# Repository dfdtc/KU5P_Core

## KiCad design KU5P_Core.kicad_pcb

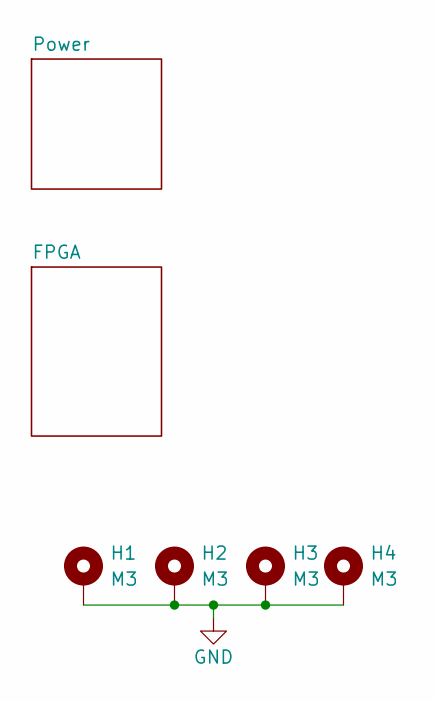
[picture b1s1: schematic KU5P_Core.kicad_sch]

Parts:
H1, H2, H3, H4: M3; MountingHole_3mm_Pad_TopBottom

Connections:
GND: H1.1 (1_1), H2.1 (1_1), H3.1 (1_1), H4.1 (1_1); also elsewhere on the board

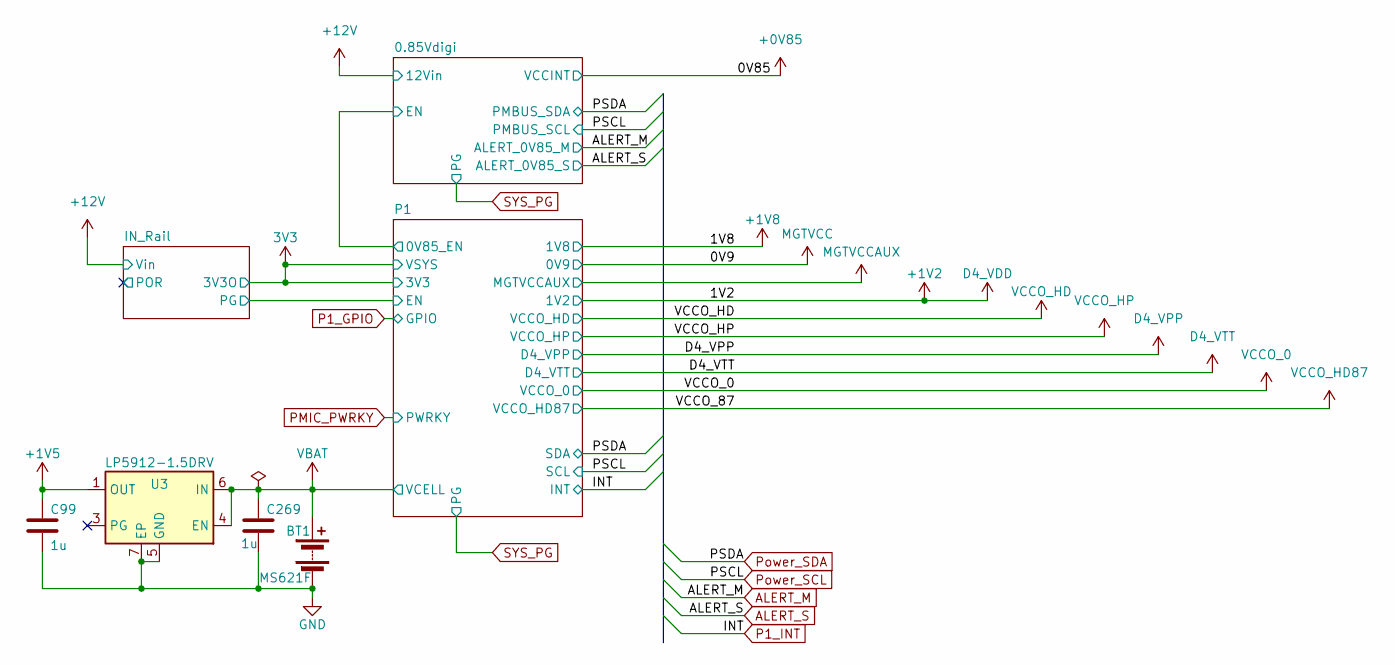
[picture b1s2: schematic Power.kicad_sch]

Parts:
BT1: MS621F; BatteryHolder_Seiko_MS621F
C99, C269: 1u; C_0402_1005Metric
U3: LP5912-1.5DRV; WSON-6-1EP_2x2mm_P0.65mm_EP1x1.6mm

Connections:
+1V5: C99.1, U3.1 (OUT); also elsewhere on the board
GND: BT1.2 (-), C99.2, C269.2, U3.5 (GND), U3.7 (EP); also elsewhere on the board
VBAT: BT1.1 (+), C269.1, U3.4 (EN), U3.6 (IN); also elsewhere on the board

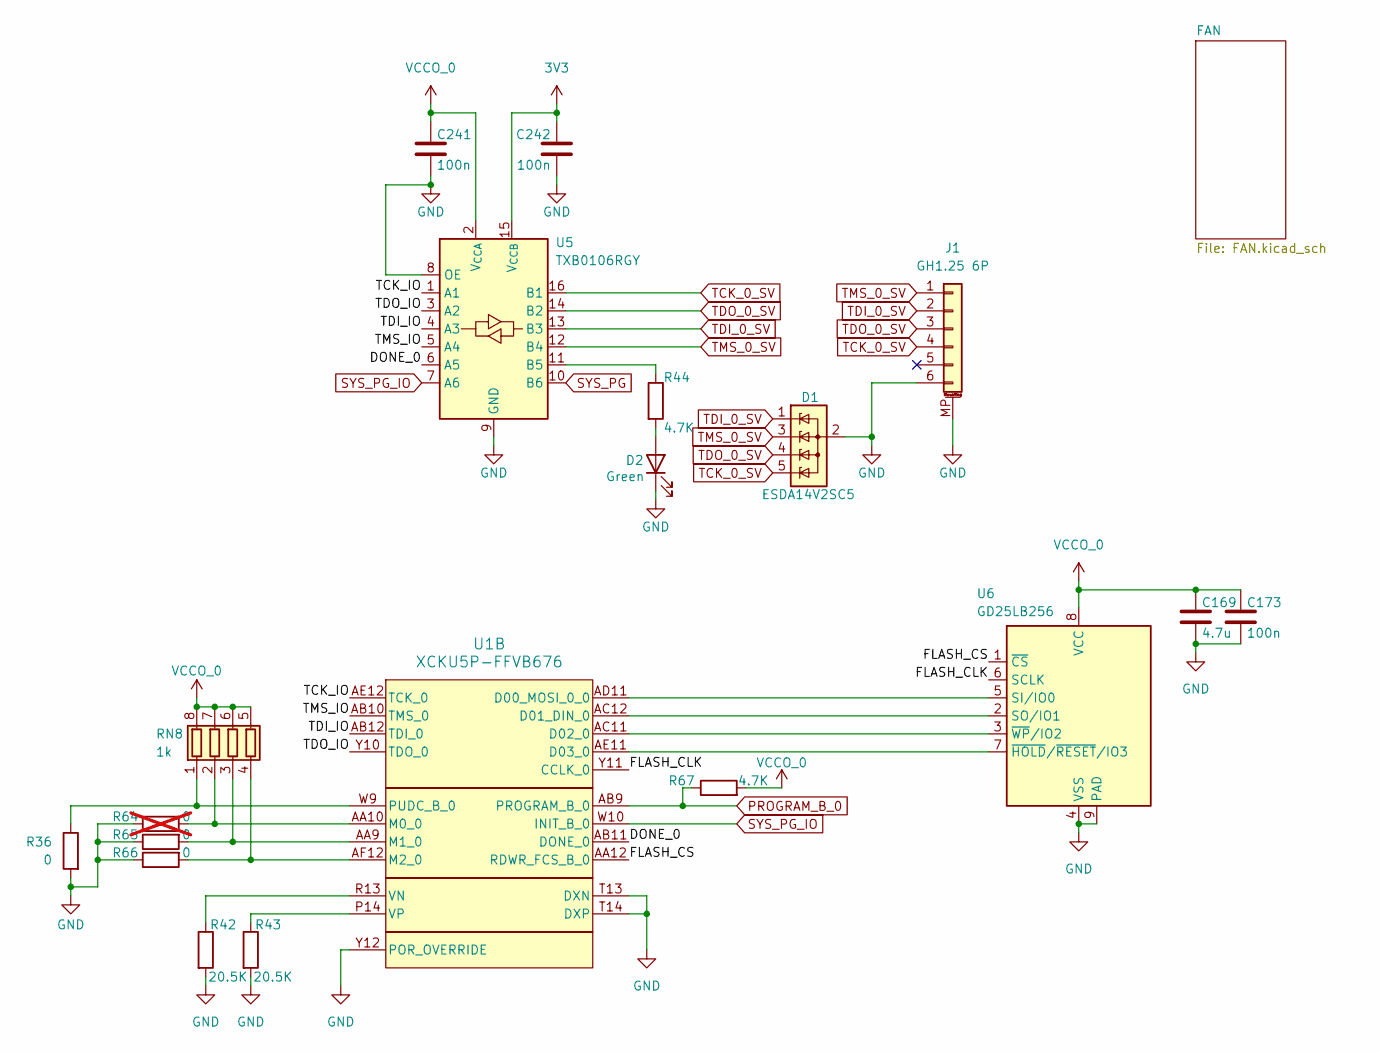
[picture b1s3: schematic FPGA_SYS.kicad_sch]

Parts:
C169: 4.7u; C_0201_0603Metric
C173, C241, C242: 100n; C_0201_0603Metric
D1: ESDA14V2SC5; SOT-23-5
D2: Green; LED_0603_1608Metric
J1: GH1.25 6P; JST_GH_SM06B-GHS-TB_1x06-1MP_P1.25mm_Horizontal
R36, R65, R66: 0; R_0402_1005Metric
R42, R43: 20.5K; R_0201_0603Metric
R44, R67: 4.7K; R_0201_0603Metric
R64: 0; R_0402_1005Metric; not fitted
RN8: 1k; R_Array_Concave_4x0402
U1: XCKU5P-FFVB676; Xilinx_FFG676
U5: TXB0106RGY; Texas_RGY_R-PVQFN-N16_EP2.05x2.55mm
U6: GD25LB256; WSON-8-1EP_8x6mm_P1.27mm_EP3.4x4.3mm

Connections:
3V3: C242.1, U5.15 (V_{CCB}); also elsewhere on the board
/FPGA/FPGA_SYS/DONE_0: U1.AB11 (DONE_0), U5.6 (A5)
/FPGA/FPGA_SYS/FLASH_CLK: U1.Y11 (CCLK_0), U6.6 (SCLK)
/FPGA/FPGA_SYS/FLASH_CS: U1.AA12 (RDWR_FCS_B_0), U6.1 (~CS)
/FPGA/FPGA_SYS/TCK_IO: U1.AE12 (TCK_0), U5.1 (A1)
/FPGA/FPGA_SYS/TDI_IO: U1.AB12 (TDI_0), U5.4 (A3)
/FPGA/FPGA_SYS/TDO_IO: U1.Y10 (TDO_0), U5.3 (A2)
/FPGA/FPGA_SYS/TMS_IO: U1.AB10 (TMS_0), U5.5 (A4)
GND: C169.2, C173.2, C241.2, C242.2, D1.2 (A), D2.1 (K), J1.6, J1.MP (MountPin), R36.2, R42.2, R43.2, R64.1, R65.1, R66.1, U1.T13 (DXN), U1.T14 (DXP), U1.Y12 (POR_OVERRIDE), U5.8 (OE), U5.9 (GND), U5.17 (GND), U6.4 (VSS), U6.9 (PAD); also elsewhere on the board
unnamed: D2.2 (A), R44.2
unnamed: R36.1, RN8.1 (R1.1), U1.W9 (PUDC_B_0)
unnamed: R64.2, RN8.2 (R2.1), U1.AA10 (M0_0)
unnamed: R65.2, RN8.3 (R3.1), U1.AA9 (M1_0)
unnamed: R66.2, RN8.4 (R4.1), U1.AF12 (M2_0)
unnamed: U1.AD11 (D00_MOSI_0_0), U6.5 (SI/IO0)
unnamed: U1.AC12 (D01_DIN_0), U6.2 (SO/IO1)
unnamed: U1.AC11 (D02_0), U6.3 (~WP/IO2)
unnamed: U1.AE11 (D03_0), U6.7 (~HOLD/~RESET/IO3)
unnamed: R42.1, U1.R13 (VN)
unnamed: R43.1, U1.P14 (VP)
unnamed: R44.1, U5.11 (B5)
PROGRAM_B_0: R67.1, U1.AB9 (PROGRAM_B_0); also elsewhere on the board
SYS_PG: U5.10 (B6); also elsewhere on the board
SYS_PG_IO: U1.W10 (INIT_B_0), U5.7 (A6)
TCK_0_SV: D1.5 (K), J1.4, U5.16 (B1)
TDI_0_SV: D1.1 (K), J1.2, U5.13 (B3)
TDO_0_SV: D1.4 (K), J1.3, U5.14 (B2)
TMS_0_SV: D1.3 (K), J1.1, U5.12 (B4)
VCCO_0: C169.1, C173.1, C241.1, R67.2, RN8.5 (R4.2), RN8.6 (R3.2), RN8.7 (R2.2), RN8.8 (R1.2), U5.2 (V_{CCA}), U6.8 (VCC); also elsewhere on the board

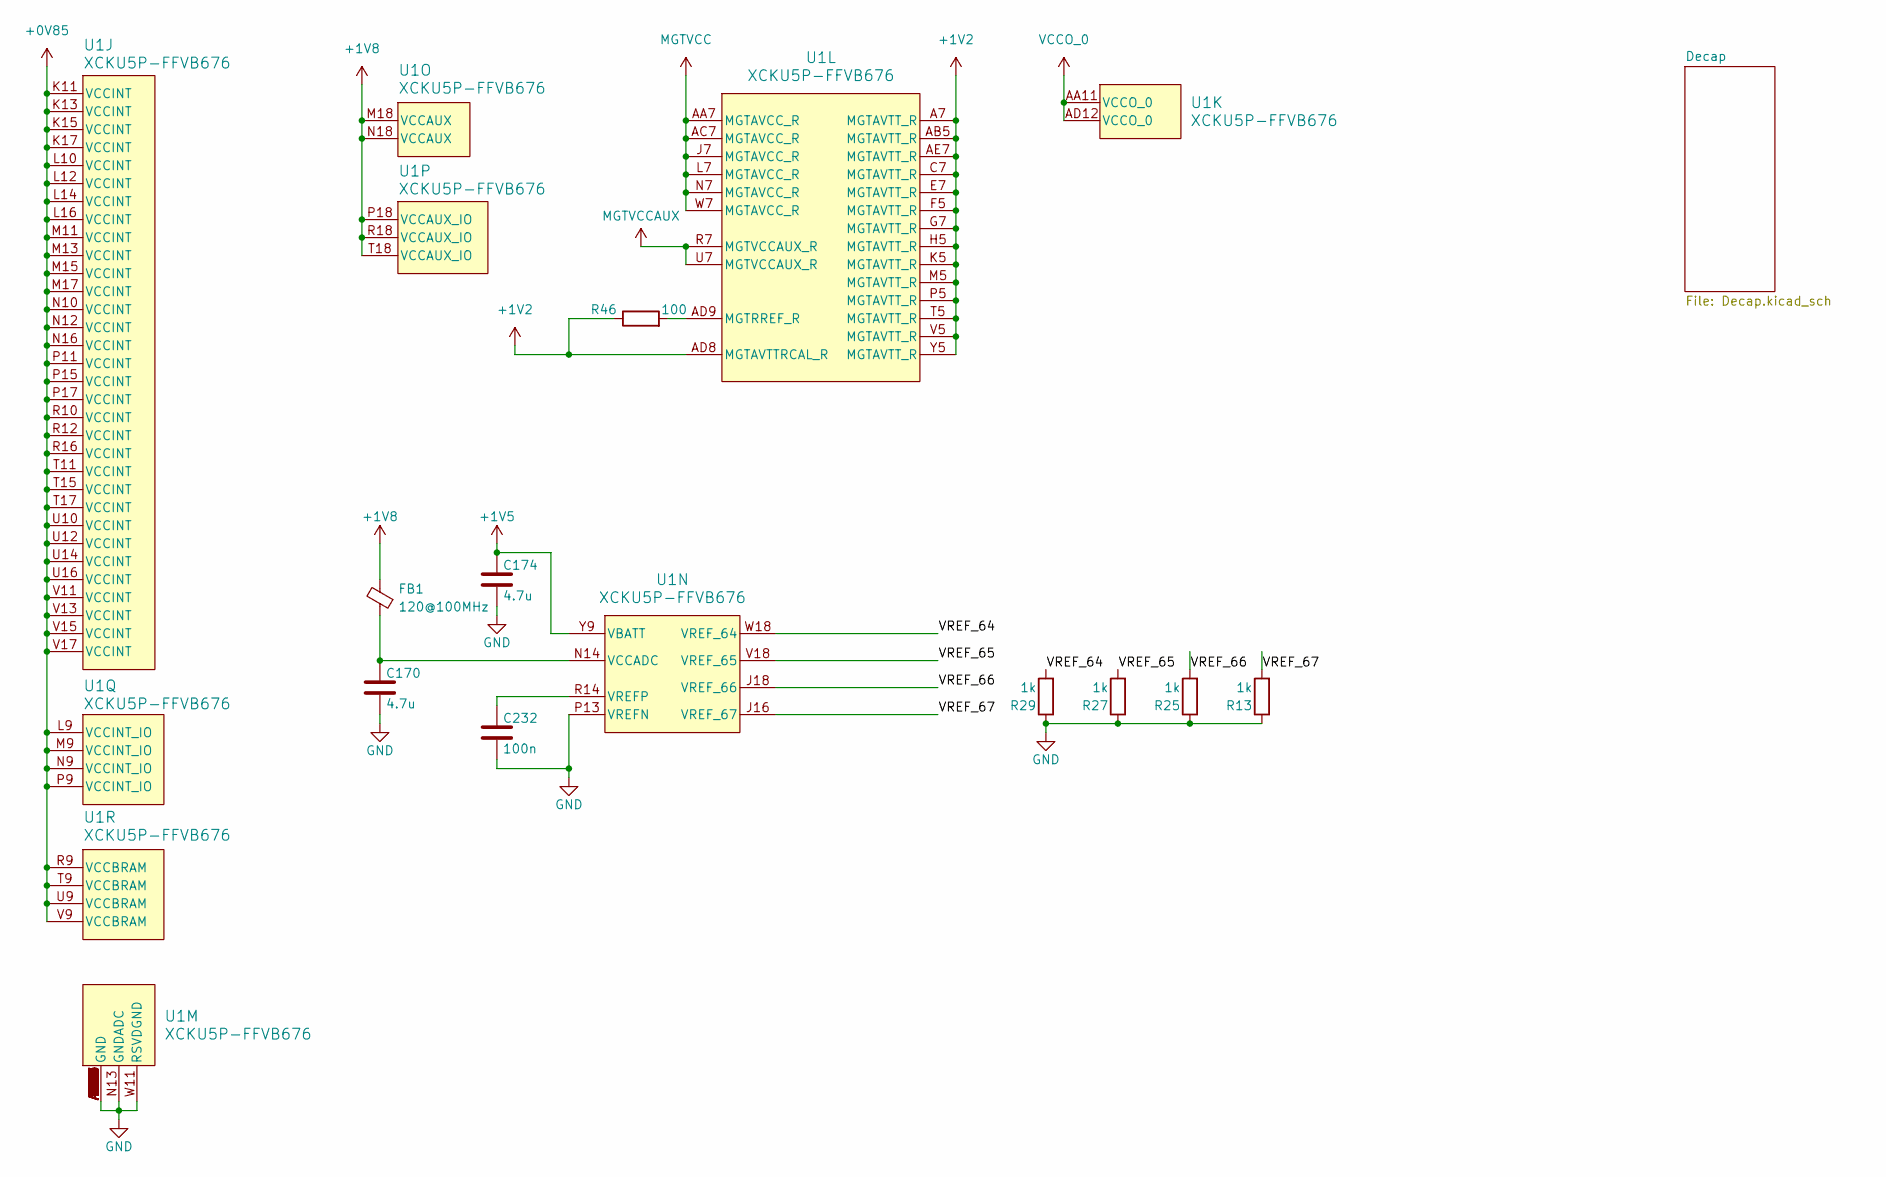
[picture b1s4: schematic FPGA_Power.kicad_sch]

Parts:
C170, C174: 4.7u; C_0201_0603Metric
C232: 100n; C_0201_0603Metric
FB1: 120@100MHz; C_0402_1005Metric
R13, R25, R27, R29: 1k; R_0201_0603Metric
R46: 100; C_0201_0603Metric
U1: XCKU5P-FFVB676; Xilinx_FFG676

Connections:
+0V85: U1.K11 (VCCINT), U1.K13 (VCCINT), U1.K15 (VCCINT), U1.K17 (VCCINT), U1.L9 (VCCINT_IO), U1.L10 (VCCINT), U1.L12 (VCCINT), U1.L14 (VCCINT), U1.L16 (VCCINT), U1.M9 (VCCINT_IO), U1.M11 (VCCINT), U1.M13 (VCCINT), U1.M15 (VCCINT), U1.M17 (VCCINT), U1.N9 (VCCINT_IO), U1.N10 (VCCINT), U1.N12 (VCCINT), U1.N16 (VCCINT), U1.P9 (VCCINT_IO), U1.P11 (VCCINT), U1.P15 (VCCINT), U1.P17 (VCCINT), U1.R9 (VCCBRAM), U1.R10 (VCCINT), U1.R12 (VCCINT), U1.R16 (VCCINT), U1.T9 (VCCBRAM), U1.T11 (VCCINT), U1.T15 (VCCINT), U1.T17 (VCCINT), U1.U9 (VCCBRAM), U1.U10 (VCCINT), U1.U12 (VCCINT), U1.U14 (VCCINT), U1.U16 (VCCINT), U1.V9 (VCCBRAM), U1.V11 (VCCINT), U1.V13 (VCCINT), U1.V15 (VCCINT), U1.V17 (VCCINT); also elsewhere on the board
+1V5: C174.1, U1.Y9 (VBATT); also elsewhere on the board
+1V8: FB1.2, U1.M18 (VCCAUX), U1.N18 (VCCAUX), U1.P18 (VCCAUX_IO), U1.R18 (VCCAUX_IO), U1.T18 (VCCAUX_IO); also elsewhere on the board
/FPGA/FPGA_Power/VREF_64: R29.2, U1.W18 (VREF_64)
/FPGA/FPGA_Power/VREF_65: R27.2, U1.V18 (VREF_65)
/FPGA/FPGA_Power/VREF_66: R25.2, U1.J18 (VREF_66)
/FPGA/FPGA_Power/VREF_67: R13.2, U1.J16 (VREF_67)
GND: C170.2, C174.2, C232.2, R13.1, R25.1, R27.1, R29.1, U1.A1 (GND), U1.A2 (GND), U1.A5 (GND), U1.A6 (GND), U1.A8 (GND), U1.A11 (GND), U1.A16 (GND), U1.A21 (GND), U1.A26 (GND), U1.AA1 (GND), U1.AA2 (GND), U1.AA3 (GND), U1.AA6 (GND), U1.AA8 (GND), U1.AA16 (GND), U1.AA26 (GND), U1.AB3 (GND), U1.AB4 (GND), U1.AB8 (GND), U1.AB13 (GND), U1.AB23 (GND), U1.AC1 (GND), U1.AC2 (GND), U1.AC3 (GND), U1.AC6 (GND), U1.AC8 (GND), U1.AC9 (GND), U1.AC10 (GND), U1.AC20 (GND), U1.AC25 (GND), U1.AD3 (GND), U1.AD4 (GND), U1.AD5 (GND), U1.AD10 (GND), U1.AD17 (GND), U1.AE1 (GND), U1.AE2 (GND), U1.AE5 (GND), U1.AE6 (GND), U1.AE10 (GND), U1.AE14 (GND), U1.AE19 (GND), U1.AE24 (GND), U1.AF3 (GND), U1.AF4 (GND), U1.AF5 (GND), U1.AF8 (GND), U1.AF9 (GND), U1.AF10 (GND), U1.AF11 (GND), U1.AF16 (GND), U1.AF21 (GND), U1.AF26 (GND), U1.B3 (GND), U1.B4 (GND), U1.B5 (GND), U1.B8 (GND), U1.B13 (GND), U1.B18 (GND), U1.B23 (GND), U1.C1 (GND), U1.C2 (GND), U1.C5 (GND), U1.C6 (GND), U1.C8 (GND), U1.C10 (GND), U1.C15 (GND), U1.C25 (GND), U1.D3 (GND), U1.D4 (GND), U1.D5 (GND), U1.D8 (GND), U1.D12 (GND), U1.D22 (GND), U1.E1 (GND), U1.E2 (GND), U1.E3 (GND), U1.E6 (GND), U1.E8 (GND), U1.E19 (GND), U1.F3 (GND), U1.F4 (GND), U1.F8 (GND), U1.F11 (GND), U1.F16 (GND), U1.F21 (GND), U1.F26 (GND), U1.G1 (GND), U1.G2 (GND), U1.G3 (GND), U1.G6 (GND), U1.G8 (GND), U1.G13 (GND), U1.G23 (GND), U1.H3 (GND), U1.H4 (GND), U1.H8 (GND), U1.H20 (GND), U1.J1 (GND), U1.J2 (GND), U1.J3 (GND), U1.J6 (GND), U1.J8 (GND), U1.J17 (GND), U1.K3 (GND), U1.K4 (GND), U1.K8 (GND), U1.K12 (GND), U1.K14 (GND), U1.K16 (GND), U1.K19 (GND), U1.K24 (GND), U1.L1 (GND), U1.L2 (GND), U1.L3 (GND), U1.L6 (GND), U1.L8 (GND), U1.L11 (GND), U1.L13 (GND), U1.L15 (GND), U1.L17 (GND), U1.L21 (GND), U1.L26 (GND), U1.M3 (GND), U1.M4 (GND), U1.M8 (GND), U1.M10 (GND), U1.M12 (GND), U1.M14 (GND), U1.M16 (GND), U1.M23 (GND), U1.N1 (GND), U1.N2 (GND), U1.N3 (GND), U1.N6 (GND), U1.N8 (GND), U1.N11 (GND), U1.N13 (GNDADC), U1.N15 (GND), U1.N17 (GND), U1.N20 (GND), U1.N25 (GND), U1.P3 (GND), U1.P4 (GND), U1.P8 (GND), U1.P10 (GND), U1.P12 (GND), U1.P13 (VREFN), U1.P16 (GND), U1.R1 (GND), U1.R2 (GND), U1.R3 (GND), U1.R6 (GND), U1.R8 (GND), U1.R11 (GND), U1.R15 (GND), U1.R17 (GND), U1.R19 (GND), U1.R24 (GND), U1.T3 (GND), U1.T4 (GND), U1.T8 (GND), U1.T10 (GND), U1.T12 (GND), U1.T16 (GND), U1.T21 (GND), U1.T26 (GND), U1.U1 (GND), U1.U2 (GND), U1.U3 (GND), U1.U6 (GND), U1.U8 (GND), U1.U11 (GND), U1.U13 (GND), U1.U15 (GND), U1.U17 (GND), U1.U18 (GND), U1.V3 (GND), U1.V4 (GND), U1.V8 (GND), U1.V10 (GND), U1.V12 (GND), U1.V14 (GND), U1.V16 (GND), U1.V20 (GND), U1.V25 (GND), U1.W1 (GND), U1.W2 (GND), U1.W3 (GND), U1.W6 (GND), U1.W8 (GND), U1.W11 (RSVDGND), U1.W17 (GND), U1.W22 (GND), U1.Y3 (GND), U1.Y4 (GND), U1.Y8 (GND), U1.Y19 (GND); also elsewhere on the board
MGTVCC: U1.AA7 (MGTAVCC_R), U1.AC7 (MGTAVCC_R), U1.J7 (MGTAVCC_R), U1.L7 (MGTAVCC_R), U1.N7 (MGTAVCC_R), U1.W7 (MGTAVCC_R); also elsewhere on the board
MGTVCCAUX: U1.R7 (MGTVCCAUX_R), U1.U7 (MGTVCCAUX_R); also elsewhere on the board
unnamed: R46.2, U1.AD9 (MGTRREF_R)
unnamed: C170.1, FB1.1, U1.N14 (VCCADC)
unnamed: C232.1, U1.R14 (VREFP)
VCCO_0: U1.AA11 (VCCO_0), U1.AD12 (VCCO_0); also elsewhere on the board

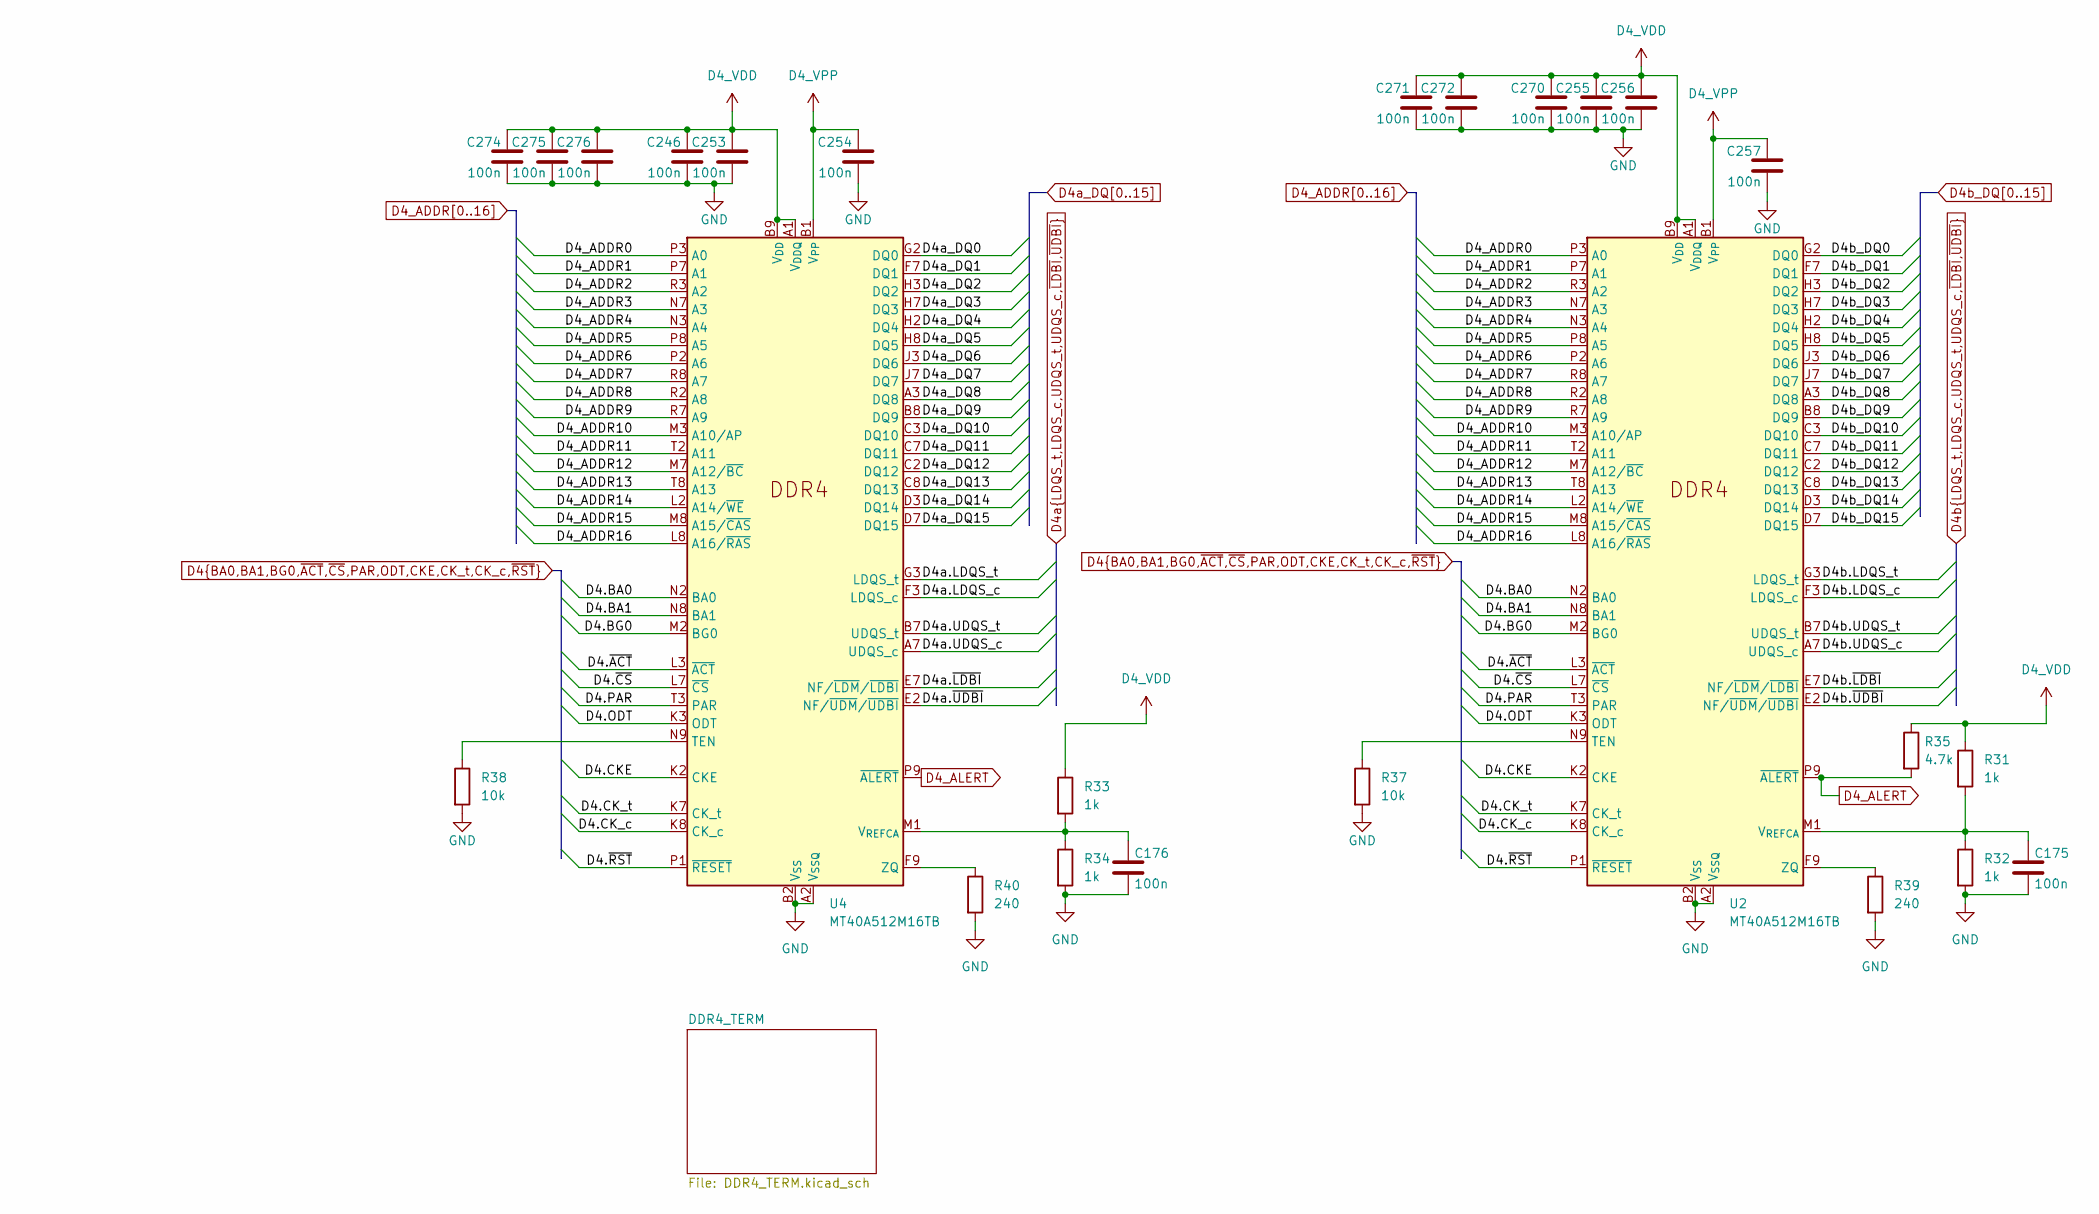
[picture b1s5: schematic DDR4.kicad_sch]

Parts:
C175, C176, C246, C253, C254, C255, C256, C257, C270, C271, C272, C274, C275, C276: 100n; C_0201_0603Metric
R31, R32, R33, R34: 1k; R_0201_0603Metric
R35: 4.7k; R_0201_0603Metric
R37, R38: 10k; R_0201_0603Metric
R39, R40: 240; R_0201_0603Metric
U2, U4: MT40A512M16TB; FBGA-96_7.5x13mm_Layout9x16_P0.8mm

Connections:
D4.BA0: U2.N2 (BA0), U4.N2 (BA0); also elsewhere on the board
D4.BA1: U2.N8 (BA1), U4.N8 (BA1); also elsewhere on the board
D4.BG0: U2.M2 (BG0), U4.M2 (BG0); also elsewhere on the board
D4.CKE: U2.K2 (CKE), U4.K2 (CKE); also elsewhere on the board
D4.CK_c: U2.K8 (CK_c), U4.K8 (CK_c); also elsewhere on the board
D4.CK_t: U2.K7 (CK_t), U4.K7 (CK_t); also elsewhere on the board
D4.ODT: U2.K3 (ODT), U4.K3 (ODT); also elsewhere on the board
D4.PAR: U2.T3 (PAR), U4.T3 (PAR); also elsewhere on the board
D4.~ACT: U2.L3 (~ACT), U4.L3 (~ACT); also elsewhere on the board
D4.~CS: U2.L7 (~CS), U4.L7 (~CS); also elsewhere on the board
D4.~RST: U2.P1 (~RESET), U4.P1 (~RESET); also elsewhere on the board
D4_ADDR0: U2.P3 (A0), U4.P3 (A0); also elsewhere on the board
D4_ADDR1: U2.P7 (A1), U4.P7 (A1); also elsewhere on the board
D4_ADDR2: U2.R3 (A2), U4.R3 (A2); also elsewhere on the board
D4_ADDR3: U2.N7 (A3), U4.N7 (A3); also elsewhere on the board
D4_ADDR4: U2.N3 (A4), U4.N3 (A4); also elsewhere on the board
D4_ADDR5: U2.P8 (A5), U4.P8 (A5); also elsewhere on the board
D4_ADDR6: U2.P2 (A6), U4.P2 (A6); also elsewhere on the board
D4_ADDR7: U2.R8 (A7), U4.R8 (A7); also elsewhere on the board
D4_ADDR8: U2.R2 (A8), U4.R2 (A8); also elsewhere on the board
D4_ADDR9: U2.R7 (A9), U4.R7 (A9); also elsewhere on the board
D4_ADDR10: U2.M3 (A10/AP), U4.M3 (A10/AP); also elsewhere on the board
D4_ADDR11: U2.T2 (A11), U4.T2 (A11); also elsewhere on the board
D4_ADDR12: U2.M7 (A12/~BC), U4.M7 (A12/~BC); also elsewhere on the board
D4_ADDR13: U2.T8 (A13), U4.T8 (A13); also elsewhere on the board
D4_ADDR14: U2.L2 (A14/~WE), U4.L2 (A14/~WE); also elsewhere on the board
D4_ADDR15: U2.M8 (A15/~CAS), U4.M8 (A15/~CAS); also elsewhere on the board
D4_ADDR16: U2.L8 (A16/~RAS), U4.L8 (A16/~RAS); also elsewhere on the board
D4_ALERT: R35.2, U2.P9 (~ALERT), U4.P9 (~ALERT)
D4_VPP: C254.1, C257.1, U2.B1 (V_{PP}), U2.R9 (V_{PP}), U4.B1 (V_{PP}), U4.R9 (V_{PP}); also elsewhere on the board
D4a.LDQS_c: U4.F3 (LDQS_c); also elsewhere on the board
D4a.LDQS_t: U4.G3 (LDQS_t); also elsewhere on the board
D4a.UDQS_c: U4.A7 (UDQS_c); also elsewhere on the board
D4a.UDQS_t: U4.B7 (UDQS_t); also elsewhere on the board
D4a.~LDBI: U4.E7 (NF/~LDM/~LDBI); also elsewhere on the board
D4a.~UDBI: U4.E2 (NF/~UDM/~UDBI); also elsewhere on the board
D4a_DQ0: U4.G2 (DQ0); also elsewhere on the board
D4a_DQ1: U4.F7 (DQ1); also elsewhere on the board
D4a_DQ2: U4.H3 (DQ2); also elsewhere on the board
D4a_DQ3: U4.H7 (DQ3); also elsewhere on the board
D4a_DQ4: U4.H2 (DQ4); also elsewhere on the board
D4a_DQ5: U4.H8 (DQ5); also elsewhere on the board
D4a_DQ6: U4.J3 (DQ6); also elsewhere on the board
D4a_DQ7: U4.J7 (DQ7); also elsewhere on the board
D4a_DQ8: U4.A3 (DQ8); also elsewhere on the board
D4a_DQ9: U4.B8 (DQ9); also elsewhere on the board
D4a_DQ10: U4.C3 (DQ10); also elsewhere on the board
D4a_DQ11: U4.C7 (DQ11); also elsewhere on the board
D4a_DQ12: U4.C2 (DQ12); also elsewhere on the board
D4a_DQ13: U4.C8 (DQ13); also elsewhere on the board
D4a_DQ14: U4.D3 (DQ14); also elsewhere on the board
D4a_DQ15: U4.D7 (DQ15); also elsewhere on the board
D4b.LDQS_c: U2.F3 (LDQS_c); also elsewhere on the board
D4b.LDQS_t: U2.G3 (LDQS_t); also elsewhere on the board
D4b.UDQS_c: U2.A7 (UDQS_c); also elsewhere on the board
D4b.UDQS_t: U2.B7 (UDQS_t); also elsewhere on the board
D4b.~LDBI: U2.E7 (NF/~LDM/~LDBI); also elsewhere on the board
D4b.~UDBI: U2.E2 (NF/~UDM/~UDBI); also elsewhere on the board
D4b_DQ0: U2.G2 (DQ0); also elsewhere on the board
D4b_DQ1: U2.F7 (DQ1); also elsewhere on the board
D4b_DQ2: U2.H3 (DQ2); also elsewhere on the board
D4b_DQ3: U2.H7 (DQ3); also elsewhere on the board
D4b_DQ4: U2.H2 (DQ4); also elsewhere on the board
D4b_DQ5: U2.H8 (DQ5); also elsewhere on the board
D4b_DQ6: U2.J3 (DQ6); also elsewhere on the board
D4b_DQ7: U2.J7 (DQ7); also elsewhere on the board
D4b_DQ8: U2.A3 (DQ8); also elsewhere on the board
D4b_DQ9: U2.B8 (DQ9); also elsewhere on the board
D4b_DQ10: U2.C3 (DQ10); also elsewhere on the board
D4b_DQ11: U2.C7 (DQ11); also elsewhere on the board
D4b_DQ12: U2.C2 (DQ12); also elsewhere on the board
D4b_DQ13: U2.C8 (DQ13); also elsewhere on the board
D4b_DQ14: U2.D3 (DQ14); also elsewhere on the board
D4b_DQ15: U2.D7 (DQ15); also elsewhere on the board
GND: C175.2, C176.2, C246.2, C253.2, C254.2, C255.2, C256.2, C257.2, C270.2, C271.2, C272.2, C274.2, C275.2, C276.2, R32.2, R34.2, R37.2, R38.2, R39.2, R40.2, U2.A2 (V_{SSQ}), U2.A8 (V_{SSQ}), U2.B2 (V_{SS}), U2.C9 (V_{SSQ}), U2.D2 (V_{SSQ}), U2.D8 (V_{SSQ}), U2.E1 (V_{SS}), U2.E3 (V_{SSQ}), U2.E8 (V_{SSQ}), U2.E9 (V_{SS}), U2.F1 (V_{SSQ}), U2.G8 (V_{SS}), U2.H1 (V_{SSQ}), U2.H9 (V_{SSQ}), U2.K1 (V_{SS}), U2.K9 (V_{SS}), U2.M9 (V_{SS}), U2.N1 (V_{SS}), U2.T1 (V_{SS}), U4.A2 (V_{SSQ}), U4.A8 (V_{SSQ}), U4.B2 (V_{SS}), U4.C9 (V_{SSQ}), U4.D2 (V_{SSQ}), U4.D8 (V_{SSQ}), U4.E1 (V_{SS}), U4.E3 (V_{SSQ}), U4.E8 (V_{SSQ}), U4.E9 (V_{SS}), U4.F1 (V_{SSQ}), U4.G8 (V_{SS}), U4.H1 (V_{SSQ}), U4.H9 (V_{SSQ}), U4.K1 (V_{SS}), U4.K9 (V_{SS}), U4.M9 (V_{SS}), U4.N1 (V_{SS}), U4.T1 (V_{SS}); also elsewhere on the board
unnamed: R37.1, U2.N9 (TEN)
unnamed: C175.1, R31.2, R32.1, U2.M1 (V_{REFCA})
unnamed: R39.1, U2.F9 (ZQ)
unnamed: R38.1, U4.N9 (TEN)
unnamed: C176.1, R33.2, R34.1, U4.M1 (V_{REFCA})
unnamed: R40.1, U4.F9 (ZQ)

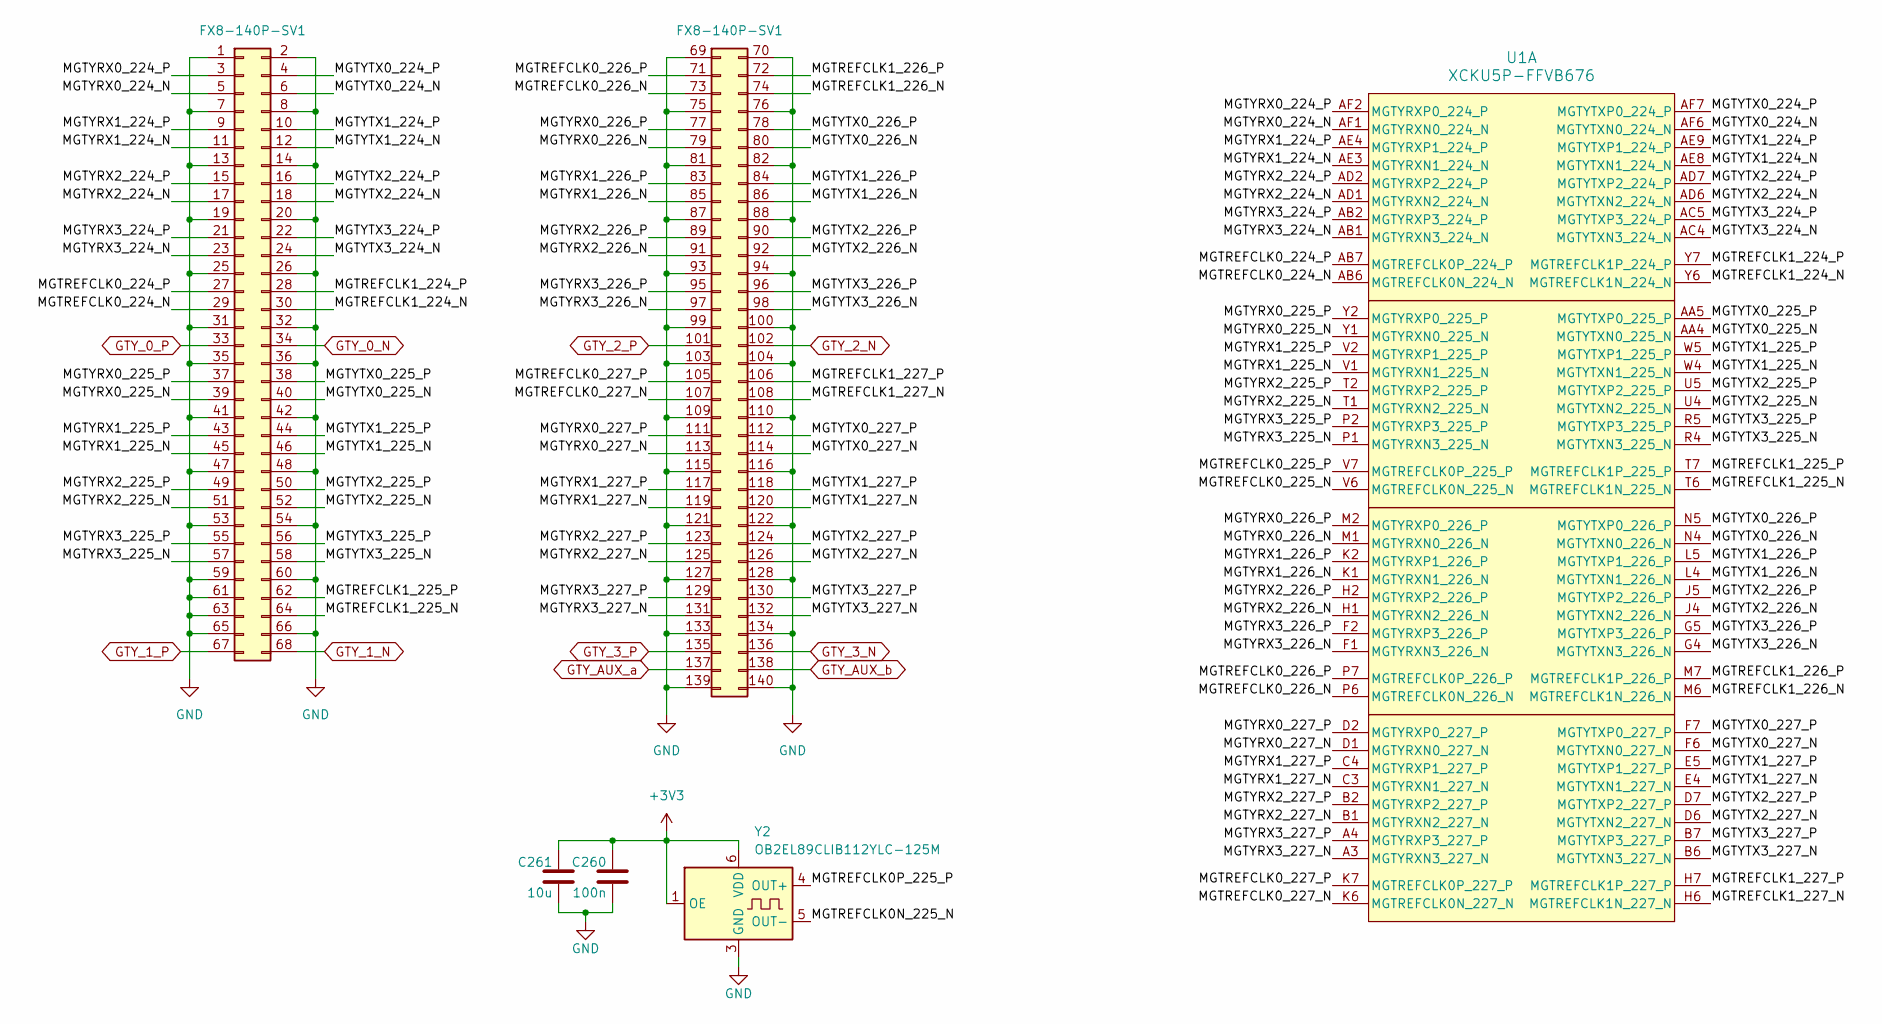
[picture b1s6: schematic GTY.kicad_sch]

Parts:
C260: 100n; C_0201_0603Metric
C261: 10u; C_0603_1608Metric
J5: FX8-140P-SV1; Hirose_FX8-140P-SV_2x70_P0.6mm
U1: XCKU5P-FFVB676; Xilinx_FFG676
Y2: OB2EL89CLIB112YLC-125M; Oscillator_SMD_SiTime_PQFD-6L_3.2x2.5mm

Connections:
+3V3: C260.1, C261.1, Y2.1 (OE), Y2.6 (VDD); also elsewhere on the board
/FPGA/GTY/MGTREFCLK0N_225_N: Y2.5 (OUT-)
/FPGA/GTY/MGTREFCLK0P_225_P: Y2.4 (OUT+)
/FPGA/GTY/MGTREFCLK0_224_N: J5.29, U1.AB6 (MGTREFCLK0N_224_N)
/FPGA/GTY/MGTREFCLK0_224_P: J5.27, U1.AB7 (MGTREFCLK0P_224_P)
/FPGA/GTY/MGTREFCLK0_225_N: U1.V6 (MGTREFCLK0N_225_N)
/FPGA/GTY/MGTREFCLK0_225_P: U1.V7 (MGTREFCLK0P_225_P)
/FPGA/GTY/MGTREFCLK0_226_N: J5.73, U1.P6 (MGTREFCLK0N_226_N)
/FPGA/GTY/MGTREFCLK0_226_P: J5.71, U1.P7 (MGTREFCLK0P_226_P)
/FPGA/GTY/MGTREFCLK0_227_N: J5.107, U1.K6 (MGTREFCLK0N_227_N)
/FPGA/GTY/MGTREFCLK0_227_P: J5.105, U1.K7 (MGTREFCLK0P_227_P)
/FPGA/GTY/MGTREFCLK1_224_N: J5.30, U1.Y6 (MGTREFCLK1N_224_N)
/FPGA/GTY/MGTREFCLK1_224_P: J5.28, U1.Y7 (MGTREFCLK1P_224_P)
/FPGA/GTY/MGTREFCLK1_225_N: J5.64, U1.T6 (MGTREFCLK1N_225_N)
/FPGA/GTY/MGTREFCLK1_225_P: J5.62, U1.T7 (MGTREFCLK1P_225_P)
/FPGA/GTY/MGTREFCLK1_226_N: J5.74, U1.M6 (MGTREFCLK1N_226_N)
/FPGA/GTY/MGTREFCLK1_226_P: J5.72, U1.M7 (MGTREFCLK1P_226_P)
/FPGA/GTY/MGTREFCLK1_227_N: J5.108, U1.H6 (MGTREFCLK1N_227_N)
/FPGA/GTY/MGTREFCLK1_227_P: J5.106, U1.H7 (MGTREFCLK1P_227_P)
/FPGA/GTY/MGTYRX0_224_N: J5.5, U1.AF1 (MGTYRXN0_224_N)
/FPGA/GTY/MGTYRX0_224_P: J5.3, U1.AF2 (MGTYRXP0_224_P)
/FPGA/GTY/MGTYRX0_225_N: J5.39, U1.Y1 (MGTYRXN0_225_N)
/FPGA/GTY/MGTYRX0_225_P: J5.37, U1.Y2 (MGTYRXP0_225_P)
/FPGA/GTY/MGTYRX0_226_N: J5.79, U1.M1 (MGTYRXN0_226_N)
/FPGA/GTY/MGTYRX0_226_P: J5.77, U1.M2 (MGTYRXP0_226_P)
/FPGA/GTY/MGTYRX0_227_N: J5.113, U1.D1 (MGTYRXN0_227_N)
/FPGA/GTY/MGTYRX0_227_P: J5.111, U1.D2 (MGTYRXP0_227_P)
/FPGA/GTY/MGTYRX1_224_N: J5.11, U1.AE3 (MGTYRXN1_224_N)
/FPGA/GTY/MGTYRX1_224_P: J5.9, U1.AE4 (MGTYRXP1_224_P)
/FPGA/GTY/MGTYRX1_225_N: J5.45, U1.V1 (MGTYRXN1_225_N)
/FPGA/GTY/MGTYRX1_225_P: J5.43, U1.V2 (MGTYRXP1_225_P)
/FPGA/GTY/MGTYRX1_226_N: J5.85, U1.K1 (MGTYRXN1_226_N)
/FPGA/GTY/MGTYRX1_226_P: J5.83, U1.K2 (MGTYRXP1_226_P)
/FPGA/GTY/MGTYRX1_227_N: J5.119, U1.C3 (MGTYRXN1_227_N)
/FPGA/GTY/MGTYRX1_227_P: J5.117, U1.C4 (MGTYRXP1_227_P)
/FPGA/GTY/MGTYRX2_224_N: J5.17, U1.AD1 (MGTYRXN2_224_N)
/FPGA/GTY/MGTYRX2_224_P: J5.15, U1.AD2 (MGTYRXP2_224_P)
/FPGA/GTY/MGTYRX2_225_N: J5.51, U1.T1 (MGTYRXN2_225_N)
/FPGA/GTY/MGTYRX2_225_P: J5.49, U1.T2 (MGTYRXP2_225_P)
/FPGA/GTY/MGTYRX2_226_N: J5.91, U1.H1 (MGTYRXN2_226_N)
/FPGA/GTY/MGTYRX2_226_P: J5.89, U1.H2 (MGTYRXP2_226_P)
/FPGA/GTY/MGTYRX2_227_N: J5.125, U1.B1 (MGTYRXN2_227_N)
/FPGA/GTY/MGTYRX2_227_P: J5.123, U1.B2 (MGTYRXP2_227_P)
/FPGA/GTY/MGTYRX3_224_N: J5.23, U1.AB1 (MGTYRXN3_224_N)
/FPGA/GTY/MGTYRX3_224_P: J5.21, U1.AB2 (MGTYRXP3_224_P)
/FPGA/GTY/MGTYRX3_225_N: J5.57, U1.P1 (MGTYRXN3_225_N)
/FPGA/GTY/MGTYRX3_225_P: J5.55, U1.P2 (MGTYRXP3_225_P)
/FPGA/GTY/MGTYRX3_226_N: J5.97, U1.F1 (MGTYRXN3_226_N)
/FPGA/GTY/MGTYRX3_226_P: J5.95, U1.F2 (MGTYRXP3_226_P)
/FPGA/GTY/MGTYRX3_227_N: J5.131, U1.A3 (MGTYRXN3_227_N)
/FPGA/GTY/MGTYRX3_227_P: J5.129, U1.A4 (MGTYRXP3_227_P)
/FPGA/GTY/MGTYTX0_224_N: J5.6, U1.AF6 (MGTYTXN0_224_N)
/FPGA/GTY/MGTYTX0_224_P: J5.4, U1.AF7 (MGTYTXP0_224_P)
/FPGA/GTY/MGTYTX0_225_N: J5.40, U1.AA4 (MGTYTXN0_225_N)
/FPGA/GTY/MGTYTX0_225_P: J5.38, U1.AA5 (MGTYTXP0_225_P)
/FPGA/GTY/MGTYTX0_226_N: J5.80, U1.N4 (MGTYTXN0_226_N)
/FPGA/GTY/MGTYTX0_226_P: J5.78, U1.N5 (MGTYTXP0_226_P)
/FPGA/GTY/MGTYTX0_227_N: J5.114, U1.F6 (MGTYTXN0_227_N)
/FPGA/GTY/MGTYTX0_227_P: J5.112, U1.F7 (MGTYTXP0_227_P)
/FPGA/GTY/MGTYTX1_224_N: J5.12, U1.AE8 (MGTYTXN1_224_N)
/FPGA/GTY/MGTYTX1_224_P: J5.10, U1.AE9 (MGTYTXP1_224_P)
/FPGA/GTY/MGTYTX1_225_N: J5.46, U1.W4 (MGTYTXN1_225_N)
/FPGA/GTY/MGTYTX1_225_P: J5.44, U1.W5 (MGTYTXP1_225_P)
/FPGA/GTY/MGTYTX1_226_N: J5.86, U1.L4 (MGTYTXN1_226_N)
/FPGA/GTY/MGTYTX1_226_P: J5.84, U1.L5 (MGTYTXP1_226_P)
/FPGA/GTY/MGTYTX1_227_N: J5.120, U1.E4 (MGTYTXN1_227_N)
/FPGA/GTY/MGTYTX1_227_P: J5.118, U1.E5 (MGTYTXP1_227_P)
/FPGA/GTY/MGTYTX2_224_N: J5.18, U1.AD6 (MGTYTXN2_224_N)
/FPGA/GTY/MGTYTX2_224_P: J5.16, U1.AD7 (MGTYTXP2_224_P)
/FPGA/GTY/MGTYTX2_225_N: J5.52, U1.U4 (MGTYTXN2_225_N)
/FPGA/GTY/MGTYTX2_225_P: J5.50, U1.U5 (MGTYTXP2_225_P)
/FPGA/GTY/MGTYTX2_226_N: J5.92, U1.J4 (MGTYTXN2_226_N)
/FPGA/GTY/MGTYTX2_226_P: J5.90, U1.J5 (MGTYTXP2_226_P)
/FPGA/GTY/MGTYTX2_227_N: J5.126, U1.D6 (MGTYTXN2_227_N)
/FPGA/GTY/MGTYTX2_227_P: J5.124, U1.D7 (MGTYTXP2_227_P)
/FPGA/GTY/MGTYTX3_224_N: J5.24, U1.AC4 (MGTYTXN3_224_N)
/FPGA/GTY/MGTYTX3_224_P: J5.22, U1.AC5 (MGTYTXP3_224_P)
/FPGA/GTY/MGTYTX3_225_N: J5.58, U1.R4 (MGTYTXN3_225_N)
/FPGA/GTY/MGTYTX3_225_P: J5.56, U1.R5 (MGTYTXP3_225_P)
/FPGA/GTY/MGTYTX3_226_N: J5.98, U1.G4 (MGTYTXN3_226_N)
/FPGA/GTY/MGTYTX3_226_P: J5.96, U1.G5 (MGTYTXP3_226_P)
/FPGA/GTY/MGTYTX3_227_N: J5.132, U1.B6 (MGTYTXN3_227_N)
/FPGA/GTY/MGTYTX3_227_P: J5.130, U1.B7 (MGTYTXP3_227_P)
GND: C260.2, C261.2, J5.1, J5.2, J5.7, J5.8, J5.13, J5.14, J5.19, J5.20, J5.25, J5.26, J5.31, J5.32, J5.35, J5.36, J5.41, J5.42, J5.47, J5.48, J5.53, J5.54, J5.59, J5.60, J5.61, J5.63, J5.65, J5.66, J5.69, J5.70, J5.75, J5.76, J5.81, J5.82, J5.87, J5.88, J5.93, J5.94, J5.99, J5.100, J5.103, J5.104, J5.109, J5.110, J5.115, J5.116, J5.121, J5.122, J5.127, J5.128, J5.133, J5.134, J5.139, J5.140, Y2.3 (GND); also elsewhere on the board
GTY_0_N: J5.34; also elsewhere on the board
GTY_0_P: J5.33; also elsewhere on the board
GTY_1_N: J5.68; also elsewhere on the board
GTY_1_P: J5.67; also elsewhere on the board
GTY_2_N: J5.102; also elsewhere on the board
GTY_2_P: J5.101; also elsewhere on the board
GTY_3_N: J5.136; also elsewhere on the board
GTY_3_P: J5.135; also elsewhere on the board
GTY_AUX_a: J5.137; also elsewhere on the board
GTY_AUX_b: J5.138; also elsewhere on the board
